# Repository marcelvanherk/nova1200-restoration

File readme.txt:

This repository is about restoration of a 1972 Data General Nova1210 computer I proudly posses.

For the journey you can read: https://hackaday.io/project/206874-making-a-1971-computer-do-ct-scan-reconstruction

It came without a frontpanel, hence creation of what is the main contents sofar.

In the mean time, this repository contains several projects:

teensy_nova: for those of you who want a tiny emulated Nova1200 computer, just add a breadboard, a Teensy (3.2, 3.2, 3.5, 4.0 or 4.1) a few switches and wires and an SDI ILI9341 TFT display (note that pinouts can differ, mines are without touch and have 9 pins on one side). Also works very nicely (no wires required) on a Featherwing 2.4 inch TFT touch display with a Feather-Teensy adaptor. On the Teensy 3.5, 4.1, or Featherwing TFT  you can add an SD card and a PS2 keyboard. Runs the 1969 Nova single user basic on the TFT display!
It can also emulate a graphics display and demonstrate CT reconstruction.

arduino_novarev1pcb: arduino code for my handwired Nova frontpanel (defunct)

arduino_novarev2pcb: arduino/teensy code for my first PCB Nova frontpanel
nova1200rev2pcb: corresponding Kikad PCB design, updated for found errors
This frontpanel is in use on my actual Nova1210 computer
See: https://www.youtube.com/watch?v=n7GDlJNpB8Y

arduino_novarev3pcb: Teensy code for my second PCB frontpanel, also simulates a Nova!
nova1200rev3pcb: corresponding Kikad PCB design
It is designed for a Teensy 3.3, but can be used with a Teensy4.0 BUT: cut track on pin 20 of U2, wire R55 and R56 to 3.3 volt instead of 5V,
This frontpanel is NOT in use on my actual Nova1210 computer (it works though) but optionally runs a Nova simulator
See: https://www.youtube.com/watch?v=eXXXlYzDSzM

lua_assembler: My first attempt at writing CT reconstruction in assembly languange. The required assembler is home written in Lua. My CT reconstruction code is assembled by this assembler
See: https://www.youtube.com/watch?v=n7GDlJNpB8Y

Note that all frontpanels and the simulator include a monitor that allows loading software. They can read the output from my Lua Nova assembler, DG punched tapes, and this Nova assembler https://github.com/Quantx/dgnsdk using the -mv format.

10 September 2020
31 October 2026

Marcel van Herk

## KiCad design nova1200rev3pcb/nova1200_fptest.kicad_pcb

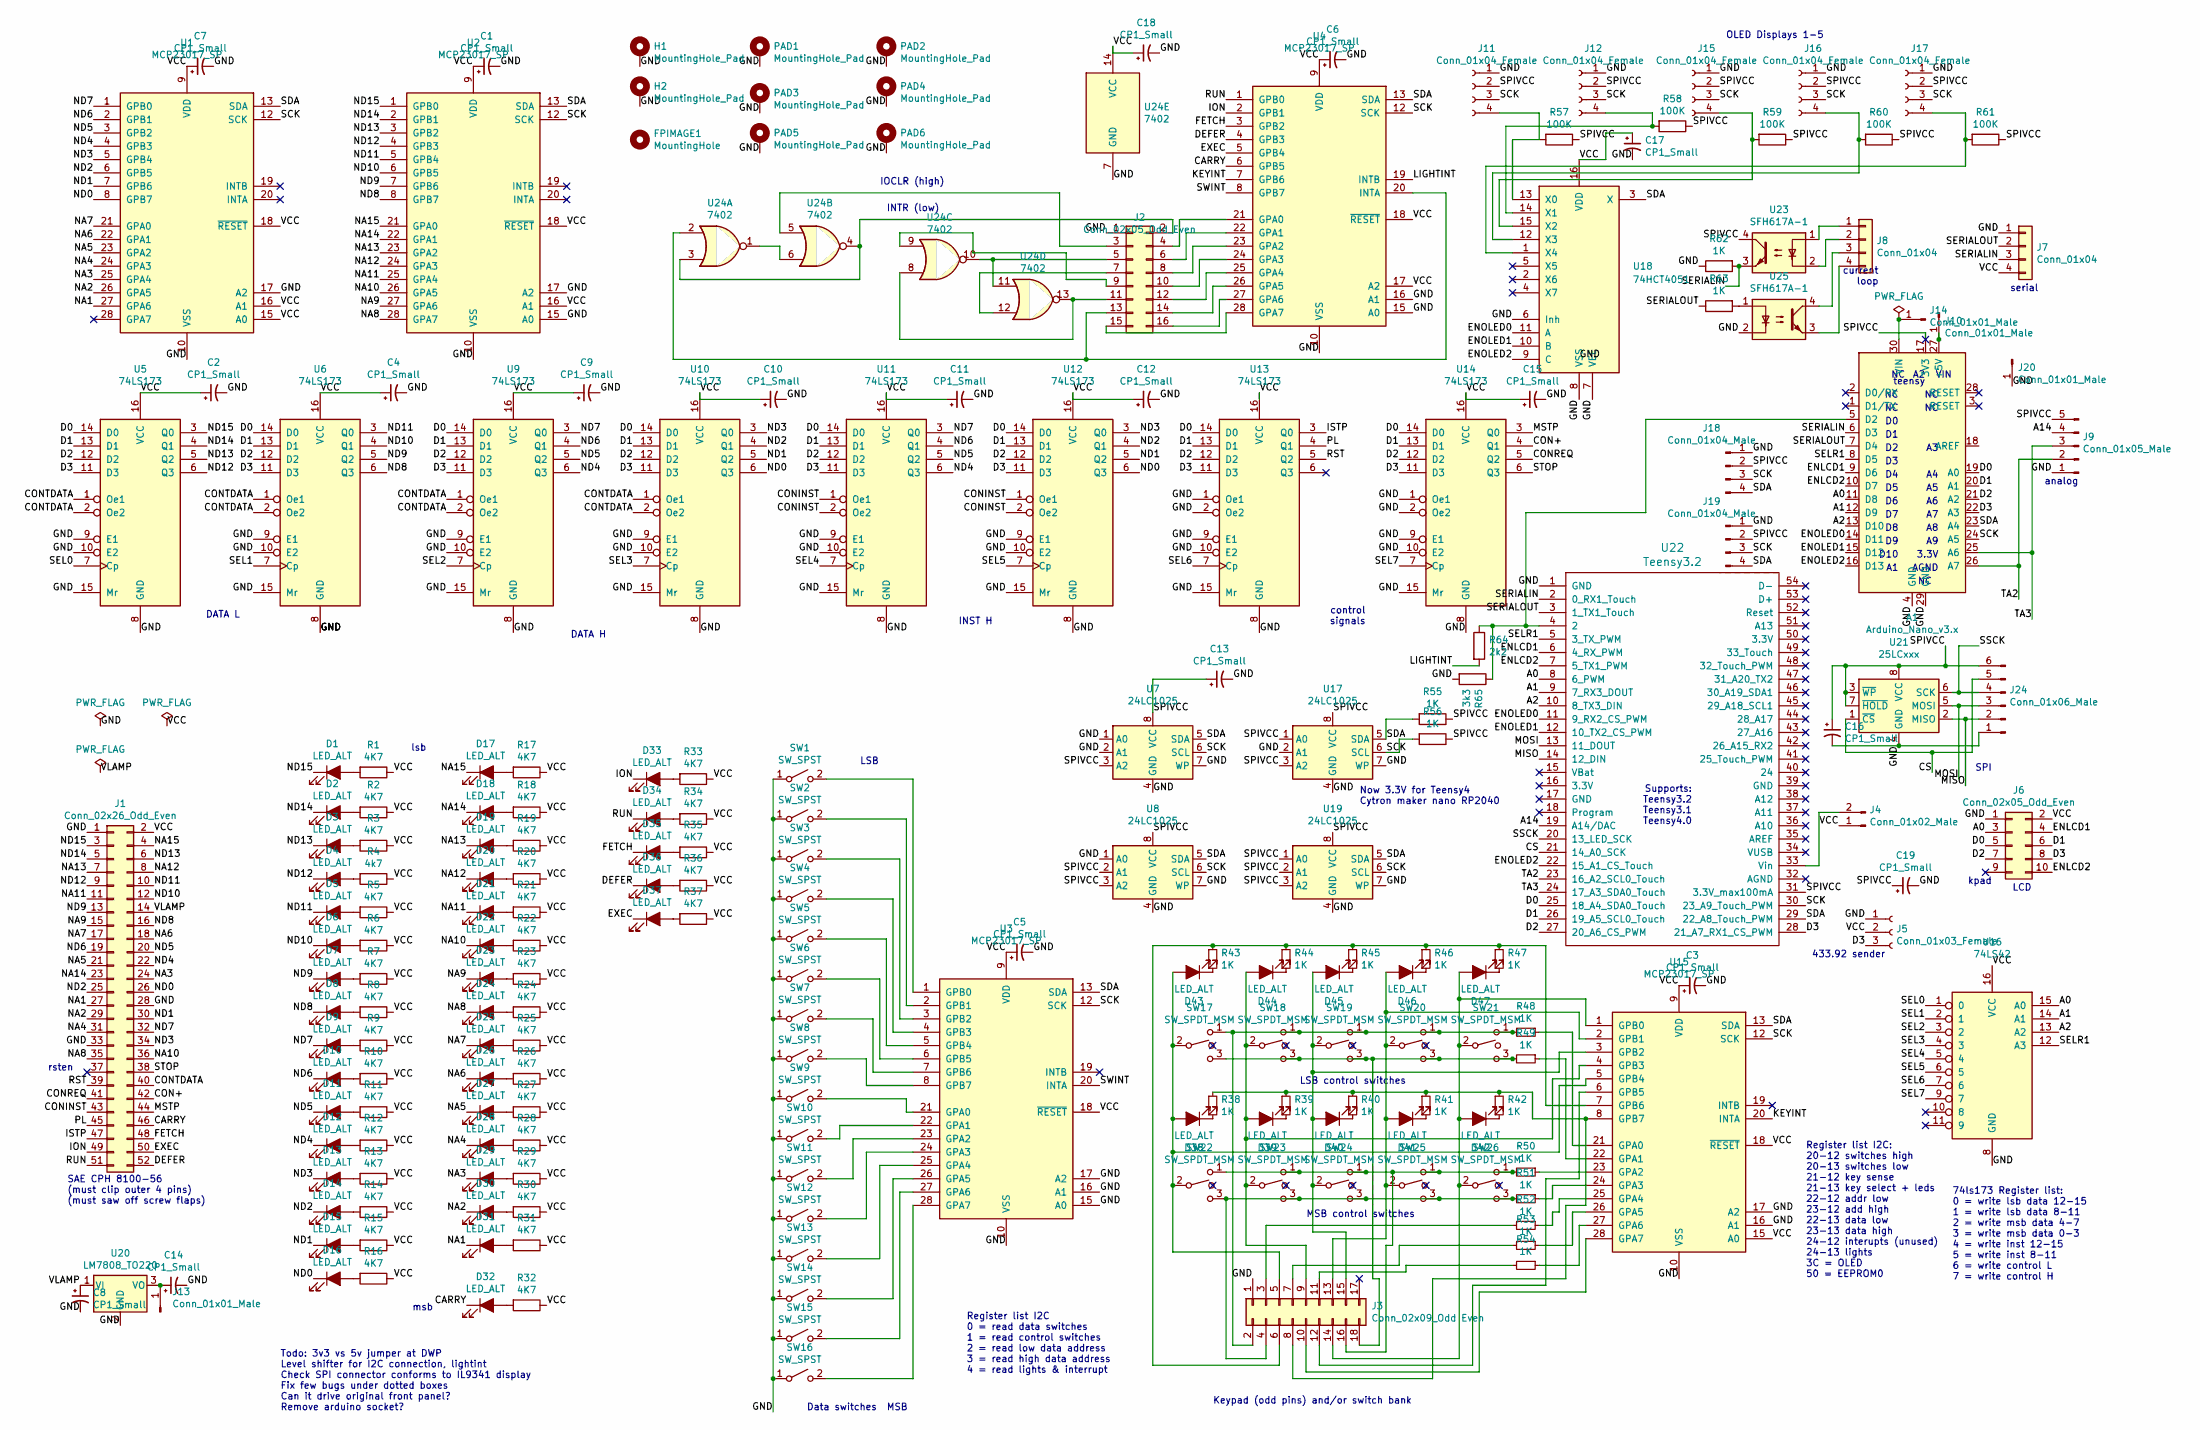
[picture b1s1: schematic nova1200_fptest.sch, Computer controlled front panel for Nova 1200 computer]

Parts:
A1: Arduino_Nano_v3.x; Arduino_Nano
C1, C2, C3, C4, C5, C6, C7, C8, C9, C10, C11, C12, C13, C14, C15, C16, C17, C18, C19: CP1_Small; CP_Radial_Tantal_D5.0mm_P5.00mm
D1, D2, D3, D4, D5, D6, D7, D8, D9, D10, D11, D12, D13, D14, D15, D16, D17, D18, D19, D20, D21, D22, D23, D24, D25, D26, D27, D28, D29, D30, D31, D32, D33, D34, D35, D36, D37, D38, D39, D40, D41, D42, D43, D44, D45, D46, D47: LED_ALT; LED_D5.0mm_Clear
FPIMAGE1: MountingHole; nova frontpanel layout
H1, H2: MountingHole_Pad; MountingHole_2.2mm_M2_Pad
J1: Conn_02x26_Odd_Even; nova_fp
J2: Conn_02x05_Odd_Even; PinHeader_2x08_P2.54mm_Vertical
J3: Conn_02x09_Odd Even; PinHeader_2x09_P2.54mm_Vertical
J4: Conn_01x02_Male; PinHeader_1x02_P2.54mm_Vertical
J5: Conn_01x03_Female; PinSocket_1x03_P2.54mm_Vertical
J6: Conn_02x05_Odd_Even; PinHeader_2x05_P2.54mm_Vertical
J7, J8: Conn_01x04; PinHeader_1x04_P2.54mm_Vertical
J9: Conn_01x05_Male; PinHeader_1x05_P2.54mm_Vertical
J10, J13, J14, J20: Conn_01x01_Male; PinHeader_1x01_P2.54mm_Vertical
J11, J12, J15, J16, J17: Conn_01x04_Female; PinSocket_1x04_P2.54mm_Vertical
J18, J19: Conn_01x04_Male; PinSocket_1x04_P2.54mm_Vertical
J24: Conn_01x06_Male; PinHeader_1x06_P2.54mm_Vertical
PAD1, PAD2, PAD3, PAD4, PAD5, PAD6: MountingHole_Pad; MountingHole_3.2mm_M3_Pad
R1, R2, R3, R5, R6, R7, R8, R9, R10, R11, R12, R13, R14, R15, R16, R17, R18, R19, R20, R21, R22, R23, R24, R25, R26, R27, R28, R29, R30, R31, R32, R33, R34, R35, R36, R37: 4K7; R_Axial_DIN0204_L3.6mm_D1.6mm_P7.62mm_Horizontal
R4: 4k7; R_Axial_DIN0204_L3.6mm_D1.6mm_P7.62mm_Horizontal
R38, R39, R40, R41, R42, R43, R44, R45, R46, R47, R48, R49, R50, R51, R52, R53, R54, R55, R56, R62, R63: 1K; R_Axial_DIN0204_L3.6mm_D1.6mm_P7.62mm_Horizontal
R57, R58, R59, R60, R61: 100K; R_Axial_DIN0204_L3.6mm_D1.6mm_P7.62mm_Horizontal
R64: 2k2; R_Axial_DIN0204_L3.6mm_D1.6mm_P7.62mm_Horizontal
R65: 3k3; R_Axial_DIN0204_L3.6mm_D1.6mm_P7.62mm_Horizontal
SW1, SW2, SW3, SW4, SW5, SW6, SW7, SW8, SW9, SW10, SW11, SW12, SW13, SW14, SW15, SW16: SW_SPST; multicomp switch
SW17, SW18, SW19, SW20, SW21, SW22, SW23, SW24, SW25, SW26: SW_SPDT_MSM; multicomp switch
U1, U2, U3, U4, U15: MCP23017_SP; DIP-28_W7.62mm
U5, U6, U9, U10, U11, U12, U13, U14: 74LS173; DIP-16_W7.62mm
U7, U8, U17, U19: 24LC1025; DIP-8_W7.62mm
U16: 74LS42; DIP-16_W7.62mm
U18: 74HCT4051; DIP-16_W7.62mm
U20: LM7808_TO220; TO-220-3_Horizontal_TabDown
U21: 25LCxxx; DIP-8_W7.62mm
U22: Teensy3.2; Teensy30_31_32_LC
U23, U25: SFH617A-1; DIP-4_W7.62mm
U24: 7402; DIP-14_W7.62mm

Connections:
/A0: A1.11 (D8), J6.3, U16.15 (A0), U22.8 (6_PWM)
/A1: A1.12 (D9), U16.14 (A1), U22.9 (7_RX3_DOUT)
/A2: A1.13 (D10), U16.13 (A2), U22.10 (8_TX3_DIN)
/A14: J9.4, U22.19 (A14/DAC)
/CARRY: D32.1 (K), J1.46, U4.6 (GPB5)
/CON+: J1.42, U14.4 (Q1)
/CONINST: J1.43, U11.1 (Oe1), U11.2 (Oe2), U12.1 (Oe1), U12.2 (Oe2)
/CONREQ: J1.41, U14.5 (Q2)
/CONTDATA: J1.40, U5.1 (Oe1), U5.2 (Oe2), U6.1 (Oe1), U6.2 (Oe2), U9.1 (Oe1), U9.2 (Oe2), U10.1 (Oe1), U10.2 (Oe2)
/CS: J24.5, U21.1 (~CS), U22.21 (14_A0_SCK)
/D0: A1.19 (A0), J6.5, U5.14 (D0), U6.14 (D0), U9.14 (D0), U10.14 (D0), U11.14 (D0), U12.14 (D0), U13.14 (D0), U14.14 (D0), U22.25 (18_A4_SDA0_Touch)
/D1: A1.20 (A1), J6.6, U5.13 (D1), U6.13 (D1), U9.13 (D1), U10.13 (D1), U11.13 (D1), U12.13 (D1), U13.13 (D1), U14.13 (D1), U22.26 (19_A5_SCL0_Touch)
/D2: A1.21 (A2), J6.7, U5.12 (D2), U6.12 (D2), U9.12 (D2), U10.12 (D2), U11.12 (D2), U12.12 (D2), U13.12 (D2), U14.12 (D2), U22.27 (20_A6_CS_PWM)
/D3: A1.22 (A3), J5.3, J6.8, U5.11 (D3), U6.11 (D3), U9.11 (D3), U10.11 (D3), U11.11 (D3), U12.11 (D3), U13.11 (D3), U14.11 (D3), U22.28 (21_A7_RX1_CS_PWM)
/DEFER: D36.1 (K), J1.52, U4.4 (GPB3)
/ENLCD1: A1.9 (D6), J6.4, U22.6 (4_RX_PWM)
/ENLCD2: A1.10 (D7), J6.10, U22.7 (5_TX1_PWM)
/ENOLED0: A1.14 (D11), U18.11 (A), U22.11 (9_RX2_CS_PWM)
/ENOLED1: A1.15 (D12), U18.10 (B), U22.12 (10_TX2_CS_PWM)
/ENOLED2: A1.16 (D13), U18.9 (C), U22.22 (15_A1_CS_Touch)
/EXEC: D37.1 (K), J1.50, U4.5 (GPB4)
/FETCH: D35.1 (K), J1.48, U4.3 (GPB2)
/GND: A1.4 (GND), A1.29 (GND), C1.2, C2.2, C3.2, C4.2, C5.2, C6.2, C7.2, C8.2, C9.2, C10.2, C11.2, C12.2, C13.2, C14.2, C15.2, C16.2, C17.2, C18.2, C19.2, H1.1, H2.1, J1.1, J1.28, J1.33, J2.1, J3.1, J5.1, J6.1, J7.1, J9.1, J11.1, J12.1, J15.1, J16.1, J17.1, J18.1, J19.1, J20.1, J24.1, PAD1.1, PAD2.1, PAD3.1, PAD4.1, PAD5.1, PAD6.1, R62.1, R65.2, SW1.1 (A), SW2.1 (A), SW3.1 (A), SW4.1 (A), SW5.1 (A), SW6.1 (A), SW7.1 (A), SW8.1 (A), SW9.1 (A), SW10.1 (A), SW11.1 (A), SW12.1 (A), SW13.1 (A), SW14.1 (A), SW15.1 (A), SW16.1 (A), U1.10 (VSS), U1.17 (A2), U2.10 (VSS), U2.15 (A0), U2.17 (A2), U3.10 (VSS), U3.15 (A0), U3.16 (A1), U3.17 (A2), U4.10 (VSS), U4.15 (A0), U4.16 (A1), U5.8 (GND), U5.9 (E1), U5.10 (E2), U5.15 (Mr), U6.8 (GND), U6.9 (E1), U6.10 (E2), U6.15 (Mr), U7.1 (A0), U7.2 (A1), U7.4 (GND), U7.7 (WP), U8.1 (A0), U8.4 (GND), U8.7 (WP), U9.8 (GND), U9.9 (E1), U9.10 (E2), U9.15 (Mr), U10.8 (GND), U10.9 (E1), U10.10 (E2), U10.15 (Mr), U11.8 (GND), U11.9 (E1), U11.10 (E2), U11.15 (Mr), U12.8 (GND), U12.9 (E1), U12.10 (E2), U12.15 (Mr), U13.1 (Oe1), U13.2 (Oe2), U13.8 (GND), U13.9 (E1), U13.10 (E2), U13.15 (Mr), U14.1 (Oe1), U14.2 (Oe2), U14.8 (GND), U14.9 (E1), U14.10 (E2), U14.15 (Mr), U15.10 (VSS), U15.16 (A1), U15.17 (A2), U16.8 (GND), U17.2 (A1), U17.4 (GND), U17.7 (WP), U18.6 (Inh), U18.7 (VEE), U18.8 (VSS), U19.4 (GND), U19.7 (WP), U20.2 (GND), U21.4 (GND), U22.1 (GND), U24.7 (GND), U25.2
/ION: D33.1 (K), J1.49, U4.2 (GPB1)
/ISTP: J1.47, U13.3 (Q0)
/KEYINT: U4.7 (GPB6), U15.20 (INTA)
/LIGHTINT: R64.2, U4.19 (INTB)
/MISO: J24.2, U21.2 (MISO), U22.14 (12_DIN)
/MOSI: J24.3, U21.5 (MOSI), U22.13 (11_DOUT)
/MSTP: J1.44, U14.3 (Q0)
/NA1: D31.1 (K), J1.27, U1.27 (GPA6)
/NA2: D30.1 (K), J1.29, U1.26 (GPA5)
/NA3: D29.1 (K), J1.24, U1.25 (GPA4)
/NA4: D28.1 (K), J1.31, U1.24 (GPA3)
/NA5: D27.1 (K), J1.21, U1.23 (GPA2)
/NA6: D26.1 (K), J1.18, U1.22 (GPA1)
/NA7: D25.1 (K), J1.17, U1.21 (GPA0)
/NA8: D24.1 (K), J1.35, U2.28 (GPA7)
/NA9: D23.1 (K), J1.15, U2.27 (GPA6)
/NA10: D22.1 (K), J1.36, U2.26 (GPA5)
/NA11: D21.1 (K), J1.11, U2.25 (GPA4)
/NA12: D20.1 (K), J1.8, U2.24 (GPA3)
/NA13: D19.1 (K), J1.7, U2.23 (GPA2)
/NA14: D18.1 (K), J1.23, U2.22 (GPA1)
/NA15: D17.1 (K), J1.4, U2.21 (GPA0)
/ND0: D16.1 (K), J1.26, U1.8 (GPB7), U10.6 (Q3), U12.6 (Q3)
/ND1: D15.1 (K), J1.30, U1.7 (GPB6), U10.5 (Q2), U12.5 (Q2)
/ND2: D14.1 (K), J1.25, U1.6 (GPB5), U10.4 (Q1), U12.4 (Q1)
/ND3: D13.1 (K), J1.34, U1.5 (GPB4), U10.3 (Q0), U12.3 (Q0)
/ND4: D12.1 (K), J1.22, U1.4 (GPB3), U9.6 (Q3), U11.6 (Q3)
/ND5: D11.1 (K), J1.20, U1.3 (GPB2), U9.5 (Q2), U11.5 (Q2)
/ND6: D10.1 (K), J1.19, U1.2 (GPB1), U9.4 (Q1), U11.4 (Q1)
/ND7: D9.1 (K), J1.32, U1.1 (GPB0), U9.3 (Q0), U11.3 (Q0)
/ND8: D8.1 (K), J1.16, U2.8 (GPB7), U6.6 (Q3)
/ND9: D7.1 (K), J1.13, U2.7 (GPB6), U6.5 (Q2)
/ND10: D6.1 (K), J1.12, U2.6 (GPB5), U6.4 (Q1)
/ND11: D5.1 (K), J1.10, U2.5 (GPB4), U6.3 (Q0)
/ND12: D4.1 (K), J1.9, U2.4 (GPB3), U5.6 (Q3)
/ND13: D3.1 (K), J1.6, U2.3 (GPB2), U5.5 (Q2)
/ND14: D2.1 (K), J1.5, U2.2 (GPB1), U5.4 (Q1)
/ND15: D1.1 (K), J1.3, U2.1 (GPB0), U5.3 (Q0)
/PL: J1.45, U13.4 (Q1)
/RST: J1.39, U13.5 (Q2)
/RUN: D34.1 (K), J1.51, U4.1 (GPB0)
/SCK: A1.24 (A5), J11.3, J12.3, J15.3, J16.3, J17.3, J18.3, J19.3, R56.2, U1.12 (SCK), U2.12 (SCK), U3.12 (SCK), U4.12 (SCK), U7.6 (SCL), U8.6 (SCL), U15.12 (SCK), U17.6 (SCL), U19.6 (SCL), U22.30 (23_A9_Touch_PWM)
/SDA: A1.23 (A4), J18.4, J19.4, R55.2, U1.13 (SDA), U2.13 (SDA), U3.13 (SDA), U4.13 (SDA), U7.5 (SDA), U8.5 (SDA), U15.13 (SDA), U17.5 (SDA), U18.3 (X), U19.5 (SDA), U22.29 (22_A8_Touch_PWM)
/SEL0: U5.7 (Cp), U16.1 (0)
/SEL1: U6.7 (Cp), U16.2 (1)
/SEL2: U9.7 (Cp), U16.3 (2)
/SEL3: U10.7 (Cp), U16.4 (3)
/SEL4: U11.7 (Cp), U16.5 (4)
/SEL5: U12.7 (Cp), U16.6 (5)
/SEL6: U13.7 (Cp), U16.7 (6)
/SEL7: U14.7 (Cp), U16.9 (7)
/SELR1: A1.8 (D5), U16.12 (A3), U22.5 (3_TX_PWM)
/SERIALIN: A1.6 (D3), J7.3, R62.2, U22.2 (0_RX1_Touch), U23.3
/SERIALOUT: A1.7 (D4), J7.2, R63.1, U22.3 (1_TX1_Touch)
/SPIVCC: A1.17 (3V3), C13.1, C16.1, C19.1, J9.5, J11.2, J12.2, J15.2, J16.2, J17.2, J18.2, J19.2, J24.6, R55.1, R56.1, R57.1, R58.1, R59.1, R60.1, R61.1, U7.3 (A2), U7.8 (VCC), U8.2 (A1), U8.3 (A2), U8.8 (VCC), U17.1 (A0), U17.3 (A2), U17.8 (VCC), U19.1 (A0), U19.2 (A1), U19.3 (A2), U19.8 (VCC), U21.3 (~WP), U21.7 (~HOLD), U21.8 (VCC), U22.31 (3.3V_max100mA), U23.4
/SSCK: J24.4, U21.6 (SCK), U22.20 (13_LED_SCK)
/STOP: J1.38, U14.6 (Q3)
/SWINT: U3.20 (INTA), U4.8 (GPB7)
/TA2: A1.26 (A7), J9.2, U22.23 (16_A2_SCL0_Touch)
/TA3: A1.25 (A6), J9.3, U22.24 (17_A3_SDA0_Touch)
/VCC: C1.1, C2.1, C3.1, C4.1, C5.1, C6.1, C7.1, C9.1, C10.1, C11.1, C12.1, C15.1, C17.1, C18.1, J1.2, J4.1, J5.2, J6.2, J7.4, R1.1, R2.1, R3.1, R4.1, R5.1, R6.1, R7.1, R8.1, R9.1, R10.1, R11.1, R12.1, R13.1, R14.1, R15.1, R16.1, R17.1, R18.1, R19.1, R20.1, R21.1, R22.1, R23.1, R24.1, R25.1, R26.1, R27.1, R28.1, R29.1, R30.1, R31.1, R32.1, R33.1, R34.1, R35.1, R36.1, R37.1, U1.9 (VDD), U1.15 (A0), U1.16 (A1), U1.18 (~RESET~), U2.9 (VDD), U2.16 (A1), U2.18 (~RESET~), U3.9 (VDD), U3.18 (~RESET~), U4.9 (VDD), U4.17 (A2), U4.18 (~RESET~), U5.16 (VCC), U6.16 (VCC), U9.16 (VCC), U10.16 (VCC), U11.16 (VCC), U12.16 (VCC), U13.16 (VCC), U14.16 (VCC), U15.9 (VDD), U15.15 (A0), U15.18 (~RESET~), U16.16 (VCC), U18.16 (VDD), U24.14 (VCC)
/VLAMP: C8.1, J1.14, U20.1 (VI)
unnamed: A1.5 (D2), R64.1, R65.1, U22.4 (2)
unnamed: A1.27 (+5V), J10.1
unnamed: A1.30 (VIN), J14.1
unnamed: C14.1, J13.1, U20.3 (VO)
unnamed: D1.2 (A), R1.2
unnamed: D2.2 (A), R2.2
unnamed: D3.2 (A), R3.2
unnamed: D4.2 (A), R4.2
unnamed: D5.2 (A), R5.2
unnamed: D6.2 (A), R6.2
unnamed: D7.2 (A), R7.2
unnamed: D8.2 (A), R8.2
unnamed: D9.2 (A), R9.2
unnamed: D10.2 (A), R10.2
unnamed: D11.2 (A), R11.2
unnamed: D12.2 (A), R12.2
unnamed: D13.2 (A), R13.2
unnamed: D14.2 (A), R14.2
unnamed: D15.2 (A), R15.2
unnamed: D16.2 (A), R16.2
unnamed: D17.2 (A), R17.2
unnamed: D18.2 (A), R18.2
unnamed: D19.2 (A), R19.2
unnamed: D20.2 (A), R20.2
unnamed: D21.2 (A), R21.2
unnamed: D22.2 (A), R22.2
unnamed: D23.2 (A), R23.2
unnamed: D24.2 (A), R24.2
unnamed: D25.2 (A), R25.2
unnamed: D26.2 (A), R26.2
unnamed: D27.2 (A), R27.2
unnamed: D28.2 (A), R28.2
unnamed: D29.2 (A), R29.2
unnamed: D30.2 (A), R30.2
unnamed: D31.2 (A), R31.2
unnamed: D32.2 (A), R32.2
unnamed: D33.2 (A), R33.2
unnamed: D34.2 (A), R34.2
unnamed: D35.2 (A), R35.2
unnamed: D36.2 (A), R36.2
unnamed: D37.2 (A), R37.2
unnamed: D38.1 (K), R38.2
unnamed: D38.2 (A), D43.2 (A), J3.5, SW17.2, SW22.2, U15.5 (GPB4)
unnamed: D39.1 (K), R39.2
unnamed: D39.2 (A), D44.2 (A), J3.9, SW18.2, SW23.2, U15.4 (GPB3)
unnamed: D40.1 (K), R40.2
unnamed: D40.2 (A), D45.2 (A), J3.15, SW19.2, SW24.2, U15.3 (GPB2)
unnamed: D41.1 (K), R41.2
unnamed: D41.2 (A), D46.2 (A), J3.13, SW20.2, SW25.2, U15.2 (GPB1)
unnamed: D42.1 (K), R42.2
unnamed: D42.2 (A), D47.2 (A), J3.14, SW21.2, SW26.2, U15.1 (GPB0)
unnamed: D43.1 (K), R43.2
unnamed: D44.1 (K), R44.2
unnamed: D45.1 (K), R45.2
unnamed: D46.1 (K), R46.2
unnamed: D47.1 (K), R47.2
unnamed: J2.2, U24.3, U24.4
unnamed: J2.3, U24.5
unnamed: J2.4, U4.21 (GPA0)
unnamed: J2.5, U24.10, U24.11
unnamed: J2.6, U4.22 (GPA1)
unnamed: J2.7, U24.12
unnamed: J2.8, U4.23 (GPA2)
unnamed: J2.9, U24.9
unnamed: J2.10, U4.24 (GPA3)
unnamed: J2.11, U24.8, U24.13
unnamed: J2.12, U4.25 (GPA4)
unnamed: J2.13, U4.20 (INTA), U24.2
unnamed: J2.14, U4.26 (GPA5)
unnamed: J2.15, U4.28 (GPA7)
unnamed: J2.16, U4.27 (GPA6)
unnamed: J3.2, R48.2, SW17.1, SW18.1, SW19.1, SW20.1, SW21.1
unnamed: J3.3, R52.2
unnamed: J3.4, R51.2, SW22.3, SW23.3, SW24.3, SW25.3, SW26.3
unnamed: J3.6, R43.1, R44.1, R45.1, R46.1, R47.1, U15.7 (GPB6)
unnamed: J3.7, R53.2
unnamed: J3.8, R38.1, R39.1, R40.1, R41.1, R42.1, U15.8 (GPB7)
unnamed: J3.10, U15.28 (GPA7)
unnamed: J3.11, R54.2
unnamed: J3.12, U15.6 (GPB5)
unnamed: J3.16, R50.2, SW22.1, SW23.1, SW24.1, SW25.1, SW26.1
unnamed: J3.18, R49.2, SW17.3, SW18.3, SW19.3, SW20.3, SW21.3
unnamed: J4.2, U22.33 (Vin)
unnamed: J8.1, U23.1
unnamed: J8.2, U23.2
unnamed: J8.3, U25.4
unnamed: J8.4, U25.3
unnamed: J11.4, R57.2, U18.13 (X0)
unnamed: J12.4, R58.2, U18.14 (X1)
unnamed: J15.4, R59.2, U18.15 (X2)
unnamed: J16.4, R60.2, U18.12 (X3)
unnamed: J17.4, R61.2, U18.1 (X4)
unnamed: R48.1, U15.21 (GPA0)
unnamed: R49.1, U15.22 (GPA1)
unnamed: R50.1, U15.23 (GPA2)
unnamed: R51.1, U15.24 (GPA3)
unnamed: R52.1, U15.25 (GPA4)
unnamed: R53.1, U15.26 (GPA5)
unnamed: R54.1, U15.27 (GPA6)
unnamed: R63.2, U25.1
unnamed: SW1.2 (B), U3.1 (GPB0)
unnamed: SW2.2 (B), U3.2 (GPB1)
unnamed: SW3.2 (B), U3.3 (GPB2)
unnamed: SW4.2 (B), U3.4 (GPB3)
unnamed: SW5.2 (B), U3.5 (GPB4)
unnamed: SW6.2 (B), U3.6 (GPB5)
unnamed: SW7.2 (B), U3.7 (GPB6)
unnamed: SW8.2 (B), U3.8 (GPB7)
unnamed: SW9.2 (B), U3.21 (GPA0)
unnamed: SW10.2 (B), U3.22 (GPA1)
unnamed: SW11.2 (B), U3.23 (GPA2)
unnamed: SW12.2 (B), U3.24 (GPA3)
unnamed: SW13.2 (B), U3.25 (GPA4)
unnamed: SW14.2 (B), U3.26 (GPA5)
unnamed: SW15.2 (B), U3.27 (GPA6)
unnamed: SW16.2 (B), U3.28 (GPA7)
unnamed: U24.1, U24.6

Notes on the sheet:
rsten
control signals
DATA L
DATA H
INST H
lsb
msb
Data switches
LSB control switches
SAE CPH 8100-56 (must clip outer 4 pins) (must saw off screw flaps)
74ls173 Register list: 0 = write lsb data 12-15 1 = write lsb data 8-11 2 = write msb data 4-7 3 = write msb data 0-3 4 = write inst 12-15 5 = write inst 8-11 6 = write control L 7 = write control H
MSB control switches
Keypad (odd pins) and/or switch bank
MSB
LSB
LCD
OLED Displays 1-5
IOCLR (high)
INTR (low)
D10
VIN
3.3V
AGND
teensy
analog
serial
kpad
SPI
Register list I2C 0 = read data switches 1 = read control switches 2 = read low data address 3 = read high data address 4 = read lights & interrupt
433.92 sender
current loop
Register list I2C: 20-12 switches high 20-13 switches low 21-12 key sense 21-13 key select + leds 22-12 addr low 23-12 add high 22-13 data low 23-13 data high 24-12 interupts (unused) 24-13 lights 3C = OLED 50 = EEPROM0
Now 3.3V for Teensy4 Cytron maker nano RP2040
Todo: 3v3 vs 5v jumper at DWP Level shifter for I2C connection, lightint Check SPI connector conforms to IL9341 display Fix few bugs under dotted boxes Can it drive original front panel? Remove arduino socket?
Supports: Teensy3.2 Teensy3.1 Teensy4.0

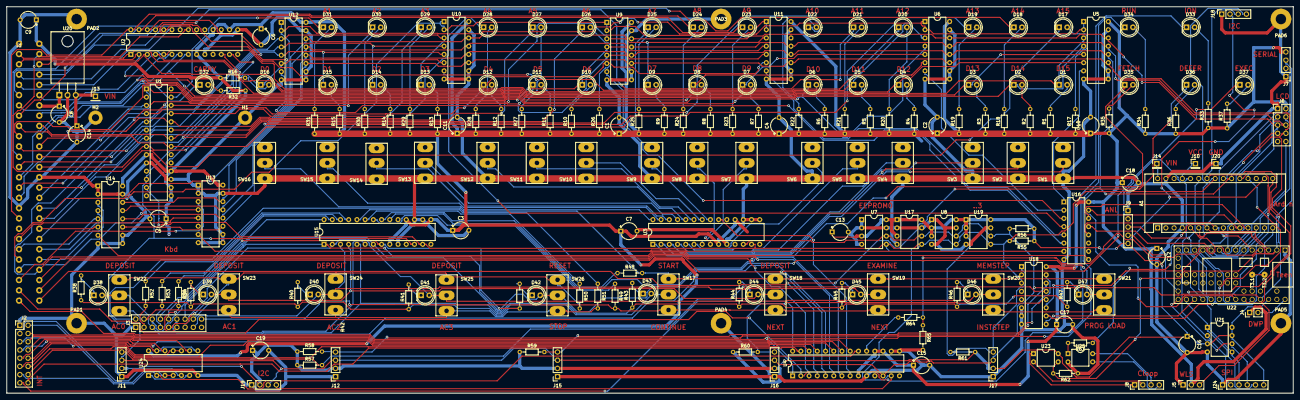
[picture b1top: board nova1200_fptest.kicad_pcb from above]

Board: 2 copper layers, 397.5 x 119.4 mm, 213 parts (0 on the bottom side), 202 nets.

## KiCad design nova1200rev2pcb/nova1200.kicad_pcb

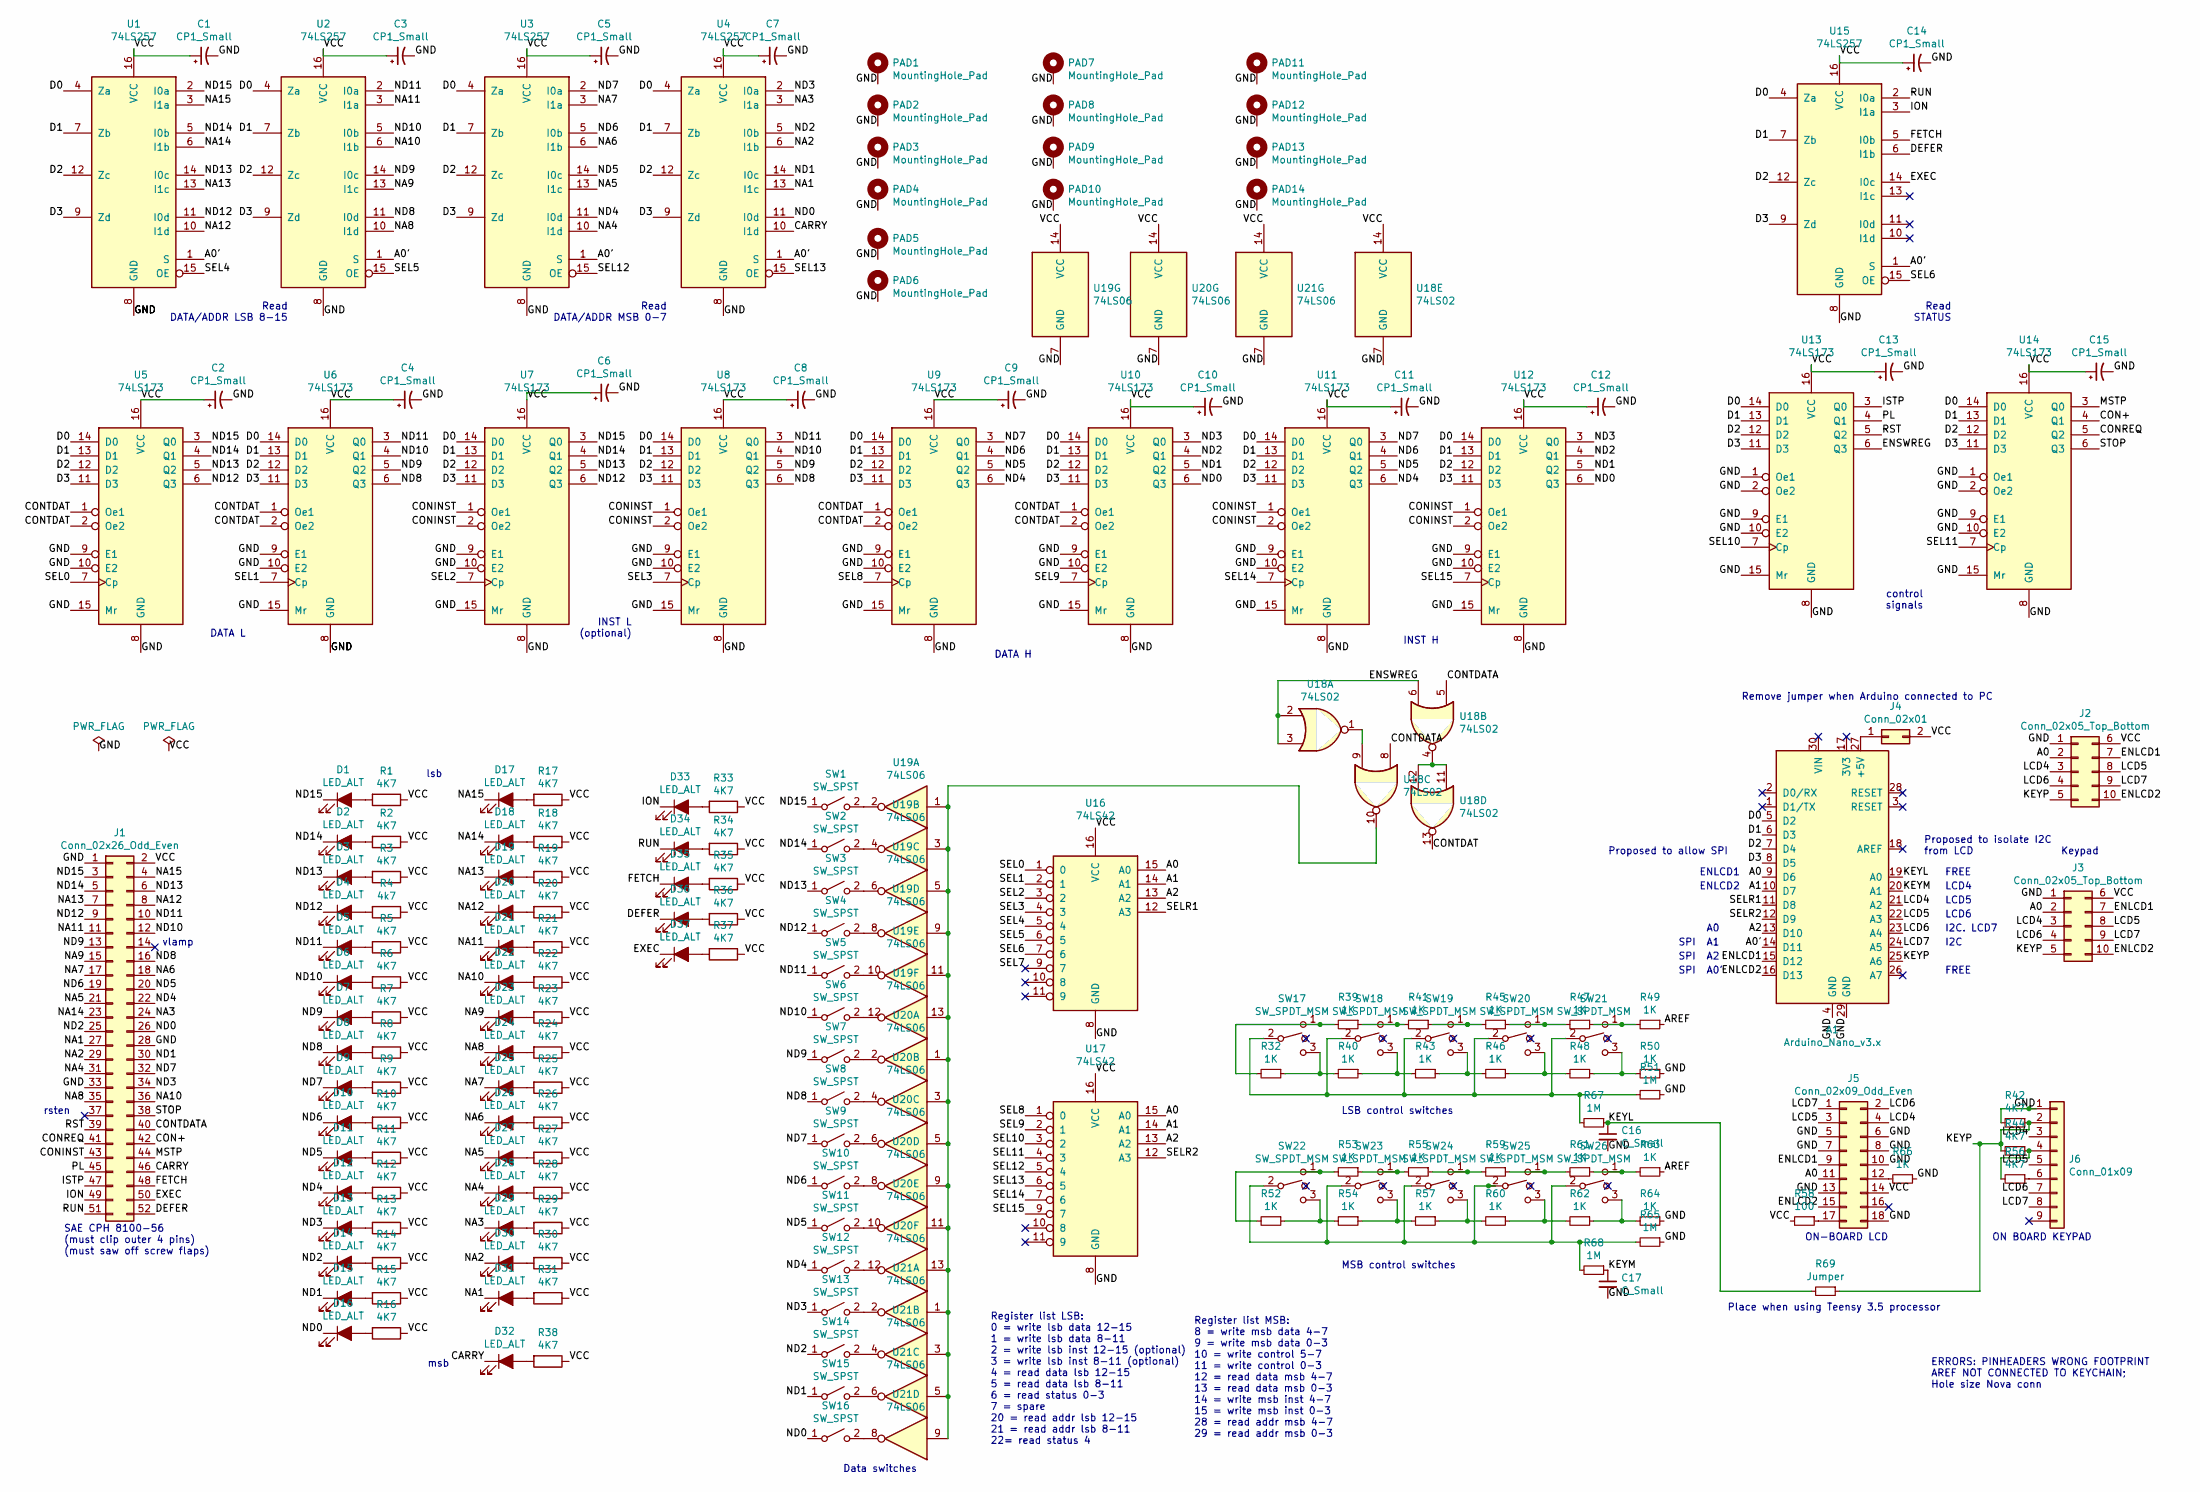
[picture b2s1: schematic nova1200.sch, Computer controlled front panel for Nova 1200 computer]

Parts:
A1: Arduino_Nano_v3.x; Arduino_Nano
C1, C2, C3, C4, C5, C6, C7, C8, C9, C10, C11, C12, C13, C14, C15: CP1_Small; CP_Radial_Tantal_D5.0mm_P5.00mm
C16, C17: C_Small; CP_Radial_D5.0mm_P2.50mm
D1, D2, D3, D4, D5, D6, D7, D8, D9, D10, D11, D12, D13, D14, D15, D16, D17, D18, D19, D20, D21, D22, D23, D24, D25, D26, D27, D28, D29, D30, D31, D32, D33, D34, D35, D36, D37: LED_ALT; LED_D5.0mm_Clear
J1: Conn_02x26_Odd_Even; nova_fp
J2, J3: Conn_02x05_Top_Bottom; PinHeader_2x05_P2.54mm_Horizontal
J4: Conn_02x01; PinHeader_1x02_P2.54mm_Vertical
J5: Conn_02x09_Odd_Even; PinHeader_2x09_P2.54mm_Vertical
J6: Conn_01x09; PinHeader_1x09_P2.54mm_Vertical
PAD1, PAD2, PAD3, PAD4, PAD5, PAD6, PAD7, PAD8, PAD9, PAD10: MountingHole_Pad; MountingHole_3.2mm_M3_Pad
PAD11, PAD12, PAD13, PAD14: MountingHole_Pad; MountingHole_2.2mm_M2_Pad
R1, R2, R3, R5, R6, R7, R8, R9, R10, R11, R12, R13, R14, R15, R16, R17, R18, R19, R20, R21, R22, R23, R24, R25, R26, R27, R28, R29, R30, R31, R33, R34, R35, R36, R37, R38, R42, R44, R56: 4K7; R_Axial_DIN0204_L3.6mm_D1.6mm_P5.08mm_Horizontal
R4: 4k7; R_Axial_DIN0204_L3.6mm_D1.6mm_P5.08mm_Horizontal
R32, R39, R40, R41, R43, R45, R46, R47, R48, R49, R50, R52, R53, R54, R55, R57, R59, R60, R61, R62, R63, R64, R66: 1K; R_Axial_DIN0204_L3.6mm_D1.6mm_P5.08mm_Horizontal
R51, R65, R67, R68: 1M; R_Axial_DIN0204_L3.6mm_D1.6mm_P5.08mm_Horizontal
R58: 100; R_Axial_DIN0204_L3.6mm_D1.6mm_P5.08mm_Horizontal
R69: Jumper; R_Axial_DIN0204_L3.6mm_D1.6mm_P5.08mm_Horizontal
SW1, SW2, SW3, SW4, SW5, SW6, SW7, SW8, SW9, SW10, SW11, SW12, SW13, SW14, SW15, SW16: SW_SPST; PinHeader_1x03_P2.54mm_Vertical
SW17, SW18, SW19, SW20, SW21, SW22, SW23, SW24, SW25, SW26: SW_SPDT_MSM; PinHeader_1x03_P2.54mm_Vertical
U1, U2, U3, U4, U15: 74LS257; DIP-16_W10.16mm
U5, U6, U7, U8, U9, U10, U11, U12, U13, U14: 74LS173; DIP-16_W10.16mm
U16, U17: 74LS42; DIP-16_W10.16mm
U18: 74LS02; DIP-14_W10.16mm
U19, U20, U21: 74LS06; DIP-14_W10.16mm

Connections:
/A0: A1.9 (D6), J2.2, J3.2, J5.11, U16.15 (A0), U17.15 (A0)
/A0': A1.14 (D11), U1.1 (S), U2.1 (S), U3.1 (S), U4.1 (S), U15.1 (S)
/A1: A1.10 (D7), U16.14 (A1), U17.14 (A1)
/A2: A1.13 (D10), U16.13 (A2), U17.13 (A2)
/AREF: R49.1, R63.1
/CARRY: D32.1 (K), J1.46, U4.10 (I1d)
/CON+: J1.42, U14.4 (Q1)
/CONINST: J1.43, U7.1 (Oe1), U7.2 (Oe2), U8.1 (Oe1), U8.2 (Oe2), U11.1 (Oe1), U11.2 (Oe2), U12.1 (Oe1), U12.2 (Oe2)
/CONREQ: J1.41, U14.5 (Q2)
/CONTDAT: U5.1 (Oe1), U5.2 (Oe2), U6.1 (Oe1), U6.2 (Oe2), U9.1 (Oe1), U9.2 (Oe2), U10.1 (Oe1), U10.2 (Oe2), U18.13
/CONTDATA: J1.40, U18.5, U18.8
/D0: A1.5 (D2), U1.4 (Za), U2.4 (Za), U3.4 (Za), U4.4 (Za), U5.14 (D0), U6.14 (D0), U7.14 (D0), U8.14 (D0), U9.14 (D0), U10.14 (D0), U11.14 (D0), U12.14 (D0), U13.14 (D0), U14.14 (D0), U15.4 (Za)
/D1: A1.6 (D3), U1.7 (Zb), U2.7 (Zb), U3.7 (Zb), U4.7 (Zb), U5.13 (D1), U6.13 (D1), U7.13 (D1), U8.13 (D1), U9.13 (D1), U10.13 (D1), U11.13 (D1), U12.13 (D1), U13.13 (D1), U14.13 (D1), U15.7 (Zb)
/D2: A1.7 (D4), U1.12 (Zc), U2.12 (Zc), U3.12 (Zc), U4.12 (Zc), U5.12 (D2), U6.12 (D2), U7.12 (D2), U8.12 (D2), U9.12 (D2), U10.12 (D2), U11.12 (D2), U12.12 (D2), U13.12 (D2), U14.12 (D2), U15.12 (Zc)
/D3: A1.8 (D5), U1.9 (Zd), U2.9 (Zd), U3.9 (Zd), U4.9 (Zd), U5.11 (D3), U6.11 (D3), U7.11 (D3), U8.11 (D3), U9.11 (D3), U10.11 (D3), U11.11 (D3), U12.11 (D3), U13.11 (D3), U14.11 (D3), U15.9 (Zd)
/DEFER: D36.1 (K), J1.52, U15.6 (I1b)
/ENLCD1: A1.15 (D12), J2.7, J3.7, J5.9
/ENLCD2: A1.16 (D13), J2.10, J3.10, J5.15
/ENSWREG: U13.6 (Q3), U18.2, U18.3, U18.6
/EXEC: D37.1 (K), J1.50, U15.14 (I0c)
/FETCH: D35.1 (K), J1.48, U15.5 (I0b)
/GND: A1.4 (GND), A1.29 (GND), C1.2, C2.2, C3.2, C4.2, C5.2, C6.2, C7.2, C8.2, C9.2, C10.2, C11.2, C12.2, C13.2, C14.2, C15.2, C16.2, C17.2, J1.1, J1.28, J1.33, J2.1, J3.1, J5.5, J5.6, J5.7, J5.8, J5.10, J5.13, J5.18, J6.1, PAD1.1, PAD2.1, PAD3.1, PAD4.1, PAD5.1, PAD6.1, PAD7.1, PAD8.1, PAD9.1, PAD10.1, PAD11.1, PAD12.1, PAD13.1, PAD14.1, R42.2, R50.1, R51.1, R64.1, R65.1, R66.1, U1.8 (GND), U2.8 (GND), U3.8 (GND), U4.8 (GND), U5.8 (GND), U5.9 (E1), U5.10 (E2), U5.15 (Mr), U6.8 (GND), U6.9 (E1), U6.10 (E2), U6.15 (Mr), U7.8 (GND), U7.9 (E1), U7.10 (E2), U7.15 (Mr), U8.8 (GND), U8.9 (E1), U8.10 (E2), U8.15 (Mr), U9.8 (GND), U9.9 (E1), U9.10 (E2), U9.15 (Mr), U10.8 (GND), U10.9 (E1), U10.10 (E2), U10.15 (Mr), U11.8 (GND), U11.9 (E1), U11.10 (E2), U11.15 (Mr), U12.8 (GND), U12.9 (E1), U12.10 (E2), U12.15 (Mr), U13.1 (Oe1), U13.2 (Oe2), U13.8 (GND), U13.9 (E1), U13.10 (E2), U13.15 (Mr), U14.1 (Oe1), U14.2 (Oe2), U14.8 (GND), U14.9 (E1), U14.10 (E2), U14.15 (Mr), U15.8 (GND), U16.8 (GND), U17.8 (GND), U18.7 (GND), U19.7 (GND), U20.7 (GND), U21.7 (GND)
/ION: D33.1 (K), J1.49, U15.3 (I1a)
/ISTP: J1.47, U13.3 (Q0)
/KEYL: A1.19 (A0), C16.1, R67.1, R69.2
/KEYM: A1.20 (A1), C17.1, R68.1
/KEYP: A1.25 (A6), J2.5, J3.5, J6.2, R42.1, R44.2, R69.1
/LCD4: A1.21 (A2), J2.3, J3.3, J5.4, J6.3
/LCD5: A1.22 (A3), J2.8, J3.8, J5.3, J6.5
/LCD6: A1.23 (A4), J2.4, J3.4, J5.2, J6.7
/LCD7: A1.24 (A5), J2.9, J3.9, J5.1, J6.8
/MSTP: J1.44, U14.3 (Q0)
/NA1: D31.1 (K), J1.27, U4.13 (I1c)
/NA2: D30.1 (K), J1.29, U4.6 (I1b)
/NA3: D29.1 (K), J1.24, U4.3 (I1a)
/NA4: D28.1 (K), J1.31, U3.10 (I1d)
/NA5: D27.1 (K), J1.21, U3.13 (I1c)
/NA6: D26.1 (K), J1.18, U3.6 (I1b)
/NA7: D25.1 (K), J1.17, U3.3 (I1a)
/NA8: D24.1 (K), J1.35, U2.10 (I1d)
/NA9: D23.1 (K), J1.15, U2.13 (I1c)
/NA10: D22.1 (K), J1.36, U2.6 (I1b)
/NA11: D21.1 (K), J1.11, U2.3 (I1a)
/NA12: D20.1 (K), J1.8, U1.10 (I1d)
/NA13: D19.1 (K), J1.7, U1.13 (I1c)
/NA14: D18.1 (K), J1.23, U1.6 (I1b)
/NA15: D17.1 (K), J1.4, U1.3 (I1a)
/ND0: D16.1 (K), J1.26, SW16.1 (A), U4.11 (I0d), U10.6 (Q3), U12.6 (Q3)
/ND1: D15.1 (K), J1.30, SW15.1 (A), U4.14 (I0c), U10.5 (Q2), U12.5 (Q2)
/ND2: D14.1 (K), J1.25, SW14.1 (A), U4.5 (I0b), U10.4 (Q1), U12.4 (Q1)
/ND3: D13.1 (K), J1.34, SW13.1 (A), U4.2 (I0a), U10.3 (Q0), U12.3 (Q0)
/ND4: D12.1 (K), J1.22, SW12.1 (A), U3.11 (I0d), U9.6 (Q3), U11.6 (Q3)
/ND5: D11.1 (K), J1.20, SW11.1 (A), U3.14 (I0c), U9.5 (Q2), U11.5 (Q2)
/ND6: D10.1 (K), J1.19, SW10.1 (A), U3.5 (I0b), U9.4 (Q1), U11.4 (Q1)
/ND7: D9.1 (K), J1.32, SW9.1 (A), U3.2 (I0a), U9.3 (Q0), U11.3 (Q0)
/ND8: D8.1 (K), J1.16, SW8.1 (A), U2.11 (I0d), U6.6 (Q3), U8.6 (Q3)
/ND9: D7.1 (K), J1.13, SW7.1 (A), U2.14 (I0c), U6.5 (Q2), U8.5 (Q2)
/ND10: D6.1 (K), J1.12, SW6.1 (A), U2.5 (I0b), U6.4 (Q1), U8.4 (Q1)
/ND11: D5.1 (K), J1.10, SW5.1 (A), U2.2 (I0a), U6.3 (Q0), U8.3 (Q0)
/ND12: D4.1 (K), J1.9, SW4.1 (A), U1.11 (I0d), U5.6 (Q3), U7.6 (Q3)
/ND13: D3.1 (K), J1.6, SW3.1 (A), U1.14 (I0c), U5.5 (Q2), U7.5 (Q2)
/ND14: D2.1 (K), J1.5, SW2.1 (A), U1.5 (I0b), U5.4 (Q1), U7.4 (Q1)
/ND15: D1.1 (K), J1.3, SW1.1 (A), U1.2 (I0a), U5.3 (Q0), U7.3 (Q0)
/PL: J1.45, U13.4 (Q1)
/RST: J1.39, U13.5 (Q2)
/RUN: D34.1 (K), J1.51, U15.2 (I0a)
/SEL0: U5.7 (Cp), U16.1 (0)
/SEL1: U6.7 (Cp), U16.2 (1)
/SEL2: U7.7 (Cp), U16.3 (2)
/SEL3: U8.7 (Cp), U16.4 (3)
/SEL4: U1.15 (OE), U16.5 (4)
/SEL5: U2.15 (OE), U16.6 (5)
/SEL6: U15.15 (OE), U16.7 (6)
/SEL7: U16.9 (7)
/SEL8: U9.7 (Cp), U17.1 (0)
/SEL9: U10.7 (Cp), U17.2 (1)
/SEL10: U13.7 (Cp), U17.3 (2)
/SEL11: U14.7 (Cp), U17.4 (3)
/SEL12: U3.15 (OE), U17.5 (4)
/SEL13: U4.15 (OE), U17.6 (5)
/SEL14: U11.7 (Cp), U17.7 (6)
/SEL15: U12.7 (Cp), U17.9 (7)
/SELR1: A1.11 (D8), U16.12 (A3)
/SELR2: A1.12 (D9), U17.12 (A3)
/STOP: J1.38, U14.6 (Q3)
/VCC: C1.1, C2.1, C3.1, C4.1, C5.1, C6.1, C7.1, C8.1, C9.1, C10.1, C11.1, C12.1, C13.1, C14.1, C15.1, J1.2, J2.6, J3.6, J4.2, J5.14, R1.1, R2.1, R3.1, R4.1, R5.1, R6.1, R7.1, R8.1, R9.1, R10.1, R11.1, R12.1, R13.1, R14.1, R15.1, R16.1, R17.1, R18.1, R19.1, R20.1, R21.1, R22.1, R23.1, R24.1, R25.1, R26.1, R27.1, R28.1, R29.1, R30.1, R31.1, R33.1, R34.1, R35.1, R36.1, R37.1, R38.1, R58.2, U1.16 (VCC), U2.16 (VCC), U3.16 (VCC), U4.16 (VCC), U5.16 (VCC), U6.16 (VCC), U7.16 (VCC), U8.16 (VCC), U9.16 (VCC), U10.16 (VCC), U11.16 (VCC), U12.16 (VCC), U13.16 (VCC), U14.16 (VCC), U15.16 (VCC), U16.16 (VCC), U17.16 (VCC), U18.14 (VCC), U19.14 (VCC), U20.14 (VCC), U21.14 (VCC)
unnamed: A1.27 (+5V), J4.1
unnamed: D1.2 (A), R1.2
unnamed: D2.2 (A), R2.2
unnamed: D3.2 (A), R3.2
unnamed: D4.2 (A), R4.2
unnamed: D5.2 (A), R5.2
unnamed: D6.2 (A), R6.2
unnamed: D7.2 (A), R7.2
unnamed: D8.2 (A), R8.2
unnamed: D9.2 (A), R9.2
unnamed: D10.2 (A), R10.2
unnamed: D11.2 (A), R11.2
unnamed: D12.2 (A), R12.2
unnamed: D13.2 (A), R13.2
unnamed: D14.2 (A), R14.2
unnamed: D15.2 (A), R15.2
unnamed: D16.2 (A), R16.2
unnamed: D17.2 (A), R17.2
unnamed: D18.2 (A), R18.2
unnamed: D19.2 (A), R19.2
unnamed: D20.2 (A), R20.2
unnamed: D21.2 (A), R21.2
unnamed: D22.2 (A), R22.2
unnamed: D23.2 (A), R23.2
unnamed: D24.2 (A), R24.2
unnamed: D25.2 (A), R25.2
unnamed: D26.2 (A), R26.2
unnamed: D27.2 (A), R27.2
unnamed: D28.2 (A), R28.2
unnamed: D29.2 (A), R29.2
unnamed: D30.2 (A), R30.2
unnamed: D31.2 (A), R31.2
unnamed: D32.2 (A), R38.2
unnamed: D33.2 (A), R33.2
unnamed: D34.2 (A), R34.2
unnamed: D35.2 (A), R35.2
unnamed: D36.2 (A), R36.2
unnamed: D37.2 (A), R37.2
unnamed: J5.12, R66.2
unnamed: J5.17, R58.1
unnamed: J6.4, R44.1, R56.2
unnamed: J6.6, R56.1
unnamed: R32.1, R40.2, SW17.3
unnamed: R32.2, R39.2, SW17.1
unnamed: R39.1, R41.2, SW18.1
unnamed: R40.1, R43.2, SW18.3
unnamed: R41.1, R45.2, SW19.1
unnamed: R43.1, R46.2, SW19.3
unnamed: R45.1, R47.2, SW20.1
unnamed: R46.1, R48.2, SW20.3
unnamed: R47.1, R49.2, SW21.1
unnamed: R48.1, R50.2, SW21.3
unnamed: R51.2, R67.2, SW17.2, SW18.2, SW19.2, SW20.2, SW21.2
unnamed: R52.1, R54.2, SW22.3
unnamed: R52.2, R53.2, SW22.1
unnamed: R53.1, R55.2, SW23.1
unnamed: R54.1, R57.2, SW23.3
unnamed: R55.1, R59.2, SW24.1
unnamed: R57.1, R60.2, SW24.3
unnamed: R59.1, R61.2, SW25.1
unnamed: R60.1, R62.2, SW25.3
unnamed: R61.1, R63.2, SW26.1
unnamed: R62.1, R64.2, SW26.3
unnamed: R65.2, R68.2, SW22.2, SW23.2, SW24.2, SW25.2, SW26.2
unnamed: SW1.2 (B), U19.2
unnamed: SW2.2 (B), U19.4
unnamed: SW3.2 (B), U19.6
unnamed: SW4.2 (B), U19.8
unnamed: SW5.2 (B), U19.10
unnamed: SW6.2 (B), U19.12
unnamed: SW7.2 (B), U20.2
unnamed: SW8.2 (B), U20.4
unnamed: SW9.2 (B), U20.6
unnamed: SW10.2 (B), U20.8
unnamed: SW11.2 (B), U20.10
unnamed: SW12.2 (B), U20.12
unnamed: SW13.2 (B), U21.2
unnamed: SW14.2 (B), U21.4
unnamed: SW15.2 (B), U21.6
unnamed: SW16.2 (B), U21.8
unnamed: U18.1, U18.9
unnamed: U18.10, U19.1, U19.3, U19.5, U19.9, U19.11, U19.13, U20.1, U20.3, U20.5, U20.9, U20.11, U20.13, U21.1, U21.3, U21.5, U21.9
unnamed: U18.4, U18.11, U18.12

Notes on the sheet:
vlamp
rsten
control signals
INST L (optional)
DATA L
DATA H
INST H
lsb
msb
Read DATA/ADDR LSB 8-15
Read DATA/ADDR MSB 0-7
Read STATUS
Remove jumper when Arduino connected to PC
Keypad
Data switches
LSB control switches
MSB control switches
ON-BOARD LCD
ON BOARD KEYPAD
SAE CPH 8100-56 (must clip outer 4 pins) (must saw off screw flaps)
Register list LSB: 0 = write lsb data 12-15 1 = write lsb data 8-11 2 = write lsb inst 12-15 (optional) 3 = write lsb inst 8-11 (optional) 4 = read data lsb 12-15 5 = read data lsb 8-11 6 = read status 0-3 7 = spare 20 = read addr lsb 12-15 21 = read addr lsb 8-11 22= read status 4
Register list MSB: 8 = write msb data 4-7 9 = write msb data 0-3 10 = write control 5-7 11 = write control 0-3 12 = read data msb 4-7 13 = read data msb 0-3 14 = write msb inst 4-7 15 = write msb inst 0-3 28 = read addr msb 4-7 29 = read addr msb 0-3
SPI
A0'
ENLCD1
ENLCD2
Proposed to allow SPI
LCD4
LCD5
LCD6
I2C. LCD7
I2C
Proposed to isolate I2C from LCD
FREE
ERRORS: PINHEADERS WRONG FOOTPRINT AREF NOT CONNECTED TO KEYCHAIN; Hole size Nova conn
Place when using Teensy 3.5 processor

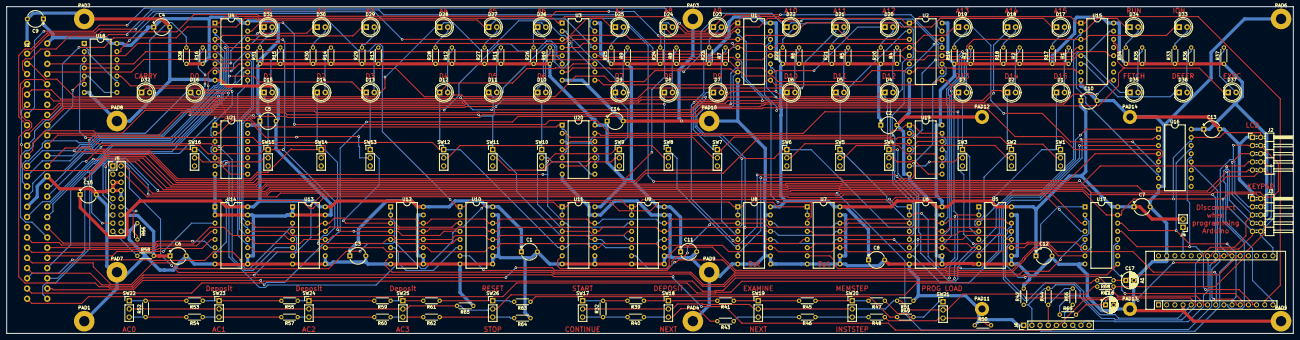
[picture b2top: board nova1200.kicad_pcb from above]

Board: 2 copper layers, 400.1 x 101.6 mm, 191 parts (0 on the bottom side), 168 nets.
